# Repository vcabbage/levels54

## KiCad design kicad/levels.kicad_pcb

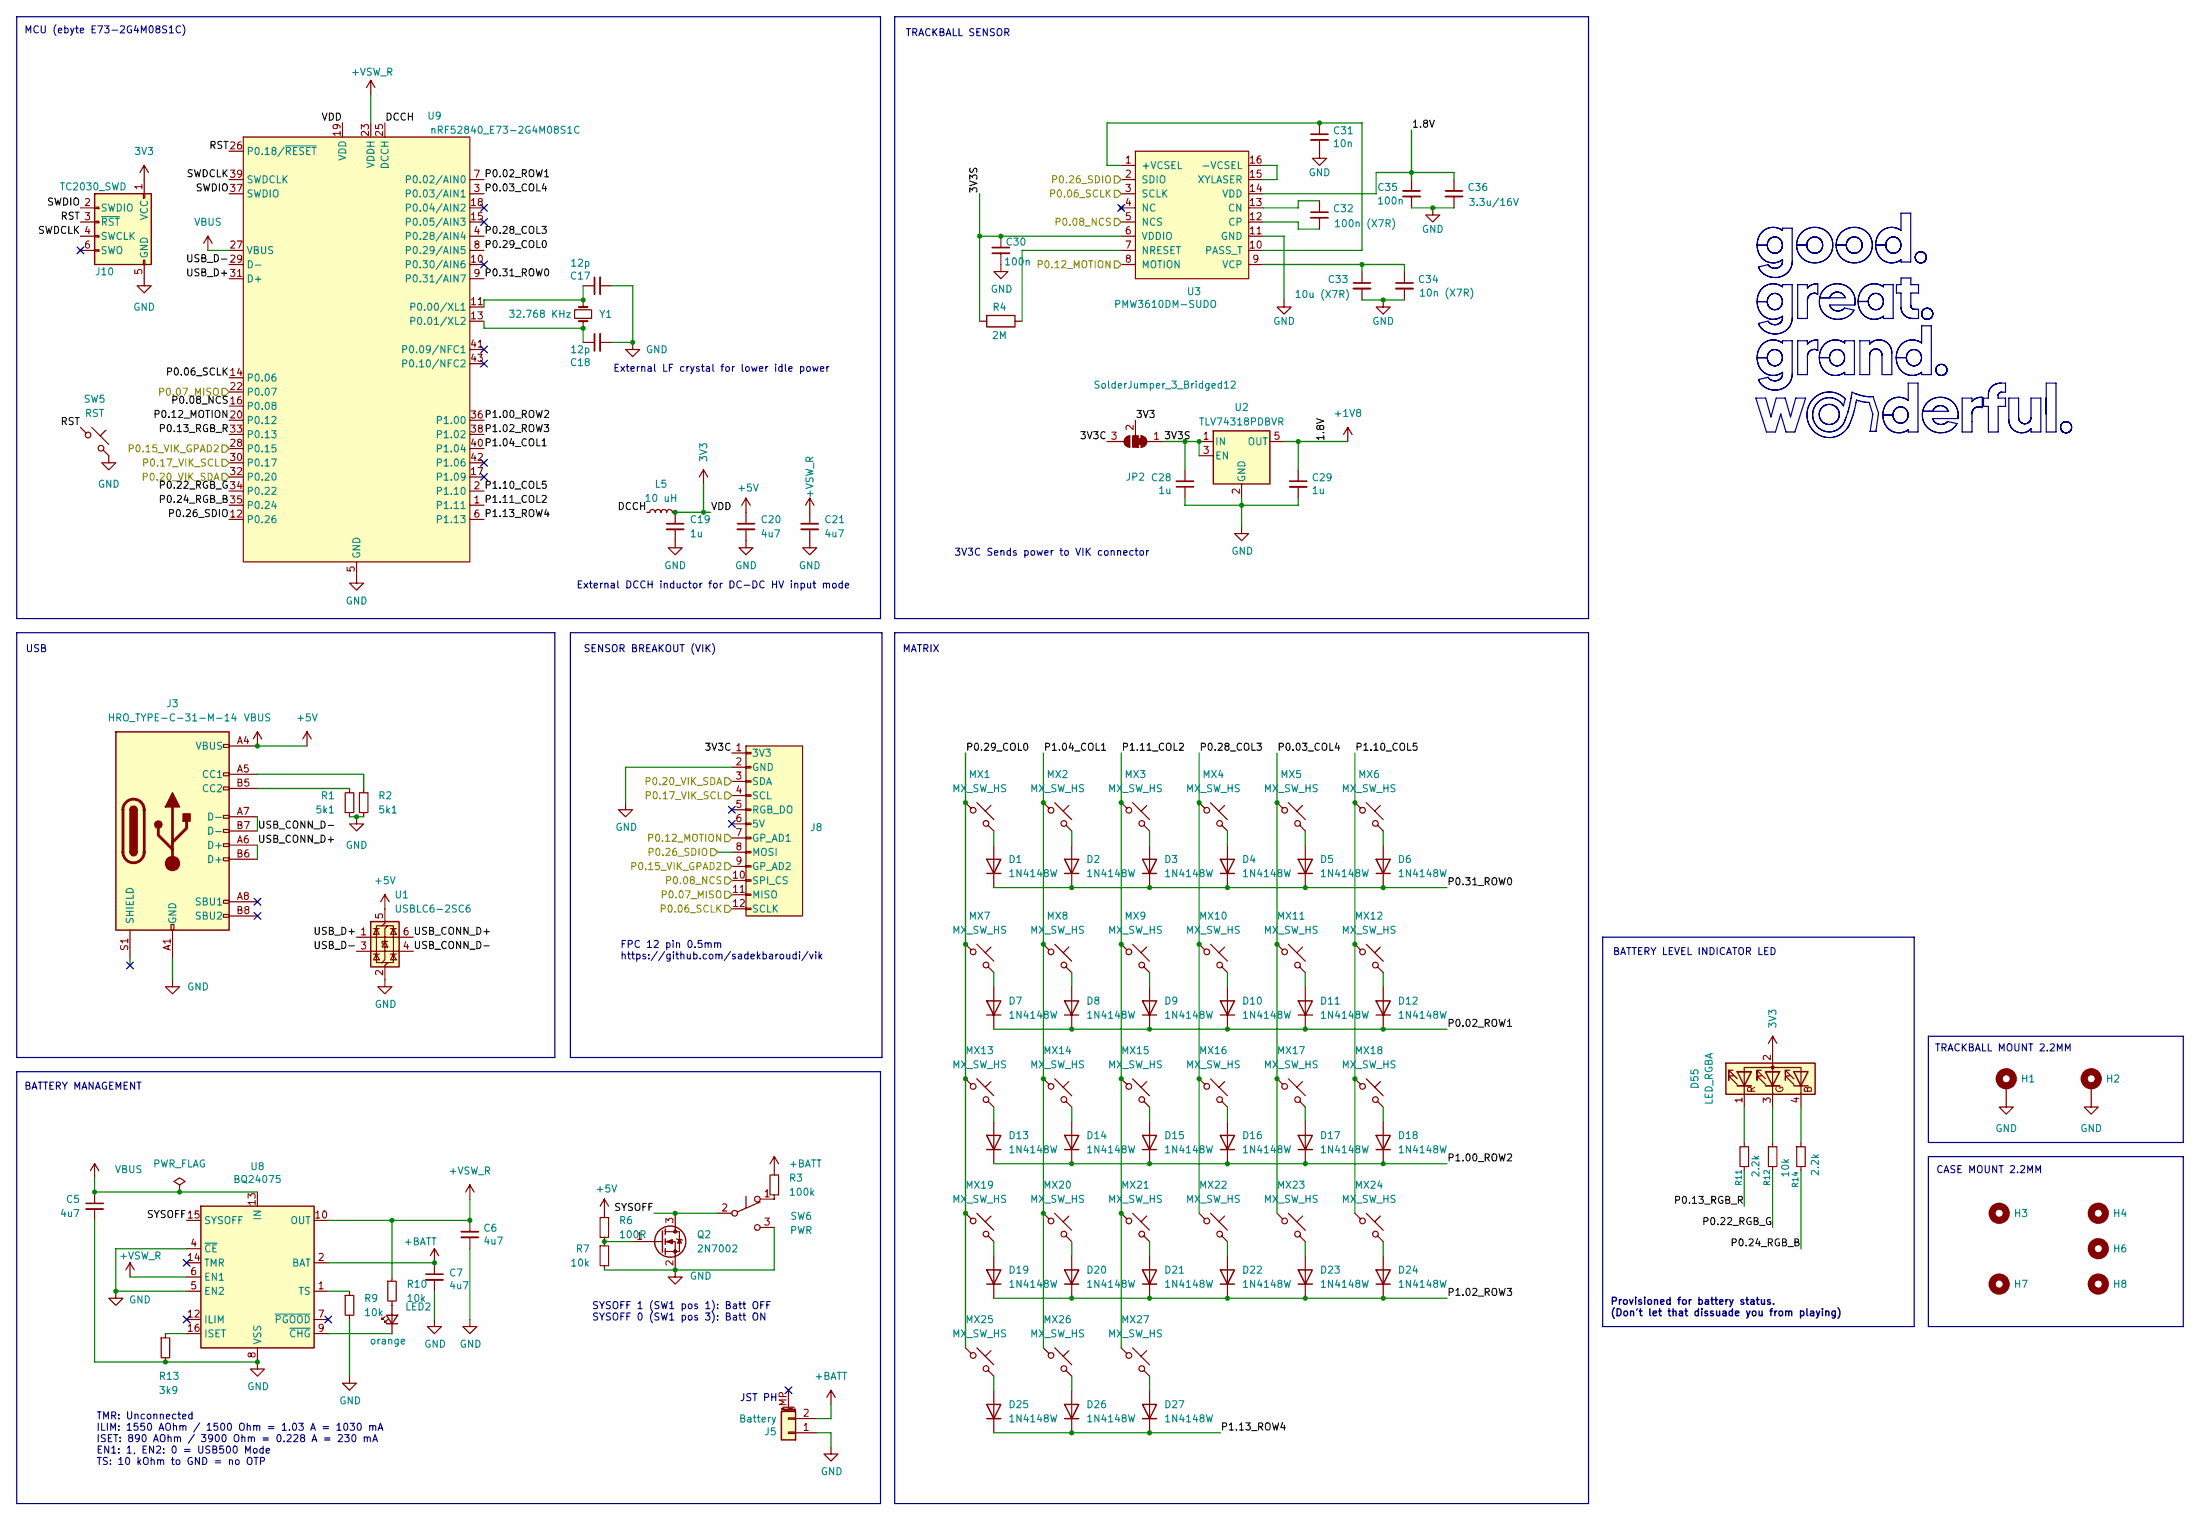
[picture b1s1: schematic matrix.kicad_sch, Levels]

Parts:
C5, C6, C7, C20, C21: 4u7; C_0402_1005Metric
C17, C18: 12p; C_0402_1005Metric
C19: 1u; C_0402_1005Metric
C28, C29: 1u; C_0603_1608Metric; LCSC C15849
C30, C35: 100n; C_0603_1608Metric; LCSC C14663
C31: 10n; C_0603_1608Metric; LCSC C57112
C32: 100n (X7R); C_0603_1608Metric; LCSC C14663
C33: 10u (X7R); C_0603_1608Metric; LCSC C237435
C34: 10n (X7R); C_0603_1608Metric; LCSC C57112
C36: 3.3u/16V; C_0603_1608Metric; LCSC C342962
D1, D2, D3, D4, D5, D6, D7, D8, D9, D10, D11, D12, D13, D14, D15, D16, D17, D18, D19, D20, D21, D22, D23, D24, D25, D26, D27: 1N4148W; D_SOD-123
D55: LED_RGBA; LED_NH-B1515RGBA-HF
H1, H2: MountingHole_Pad; MountingHole_2.2mm_M2_ISO7380_Pad
H3, H4, H6, H7: MountingHole; MountingHole_3.2mm_M3_DIN965
H8: MountingHole; MountingHole_2.2mm_M2_ISO7380
J3: HRO_TYPE-C-31-M-14; USB_C_Receptacle_HRO_TYPE-C-31-M-14
J5: Battery; JST_PH_S2B-PH-K_1x02_P2.00mm_Horizontal; LCSC C505023
J8: vik-keyboard-connector-horizontal
J10: TC2030_SWD; CON_TC2030_outlined
JP2: SolderJumper_3_Bridged12; SolderJumper-3_P1.3mm_Bridged12_RoundedPad1.0x1.5mm_NumberL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
L5: 10 uH; L_0603_1608Metric; LCSC C92982
LED2: orange; LED_0402_1005Metric
MX1, MX2, MX3, MX4, MX5, MX6, MX7, MX8, MX9, MX10, MX11, MX12, MX13, MX14, MX15, MX16, MX17, MX18, MX19, MX20, MX21, MX22, MX23, MX24, MX25, MX26, MX27: MX_SW_HS; SW_MX_HS_CPG151101S11_1u
Q2: 2N7002; SOT-23
R1, R2: 5k1; R_0402_1005Metric
R3: 100k; R_0402_1005Metric
R4: 2M; R_0603_1608Metric; LCSC C22976
R6: 100R; R_0402_1005Metric
R7, R9, R10, R12: 10k; R_0402_1005Metric
R11, R14: 2.2k; R_0402_1005Metric
R13: 3k9; R_0402_1005Metric
SW5: RST; SW_SPST_SKQG_WithStem
SW6: PWR; SW_MSK12C02-HB
U1: USBLC6-2SC6; SOT-23-6
U2: TLV74318PDBVR; SOT-23-5; LCSC C485152
U3: PMW3610DM-SUDO; PMW3610DM-SUDU 16Pin
U8: BQ24075; VQFN-16-1EP_3x3mm_P0.5mm_EP1.6x1.6mm
U9: nRF52840_E73-2G4M08S1C; LCSC C356849
Y1: 32.768 KHz; Crystal_SMD_2012-2Pin_2.0x1.2mm; LCSC C55208

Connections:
3V3: C19.1, D55.2 (A), J10.1 (VCC), JP2.2 (C), L5.2, U9.19 (VDD); also elsewhere on the board
+1V8: C29.1, C35.1, C36.1, U2.5 (OUT), U3.14 (VDD); also elsewhere on the board
+5V: C5.1, C20.1, J3.A4 (VBUS), J3.A9 (VBUS), J3.B4 (VBUS), J3.B9 (VBUS), R6.1, U1.5 (VBUS), U8.13 (IN), U9.27 (VBUS); also elsewhere on the board
+BATT: C7.1, J5.2, R3.2, U8.2 (BAT), U8.3 (BAT); also elsewhere on the board
+VSW_R: C6.1, C21.1, R10.1, U8.6 (EN1), U8.10 (OUT), U8.11 (OUT), U9.23 (VDDH)
/Right/3V3C: J8.1 (3V3), JP2.3 (B)
/Right/3V3S: C28.2, C30.1, JP2.1 (A), R4.2, U2.1 (IN), U2.3 (EN), U3.6 (VDDIO)
/Right/DCCH: L5.1, U9.25 (DCCH)
/Right/P0.02_ROW1: D7.1 (K), D8.1 (K), D9.1 (K), D10.1 (K), D11.1 (K), D12.1 (K), U9.7 (P0.02/AIN0)
/Right/P0.03_COL4: MX5.1, MX11.1, MX17.1, MX23.1, U9.3 (P0.03/AIN1)
/Right/P0.06_SCLK: J8.12 (SCLK), U3.3 (SCLK), U9.14 (P0.06)
/Right/P0.07_MISO: J8.11 (MISO), U9.22 (P0.07)
/Right/P0.08_NCS: J8.10 (SPI_CS), U3.5 (NCS), U9.16 (P0.08)
/Right/P0.12_MOTION: J8.7 (GP_AD1), U3.8 (MOTION), U9.20 (P0.12)
/Right/P0.13_RGB_R: R11.1, U9.33 (P0.13)
/Right/P0.15_VIK_GPAD2: J8.9 (GP_AD2), U9.28 (P0.15)
/Right/P0.17_VIK_SCL: J8.4 (SCL), U9.30 (P0.17)
/Right/P0.20_VIK_SDA: J8.3 (SDA), U9.32 (P0.20)
/Right/P0.22_RGB_G: R12.2, U9.34 (P0.22)
/Right/P0.24_RGB_B: R14.2, U9.35 (P0.24)
/Right/P0.26_SDIO: J8.8 (MOSI), U3.2 (SDIO), U9.12 (P0.26)
/Right/P0.28_COL3: MX4.1, MX10.1, MX16.1, MX22.1, U9.4 (P0.28/AIN4)
/Right/P0.29_COL0: MX1.1, MX7.1, MX13.1, MX19.1, MX25.1, U9.8 (P0.29/AIN5)
/Right/P0.31_ROW0: D1.1 (K), D2.1 (K), D3.1 (K), D4.1 (K), D5.1 (K), D6.1 (K), U9.9 (P0.31/AIN7)
/Right/P1.00_ROW2: D13.1 (K), D14.1 (K), D15.1 (K), D16.1 (K), D17.1 (K), D18.1 (K), U9.36 (P1.00)
/Right/P1.02_ROW3: D19.1 (K), D20.1 (K), D21.1 (K), D22.1 (K), D23.1 (K), D24.1 (K), U9.38 (P1.02)
/Right/P1.04_COL1: MX2.1, MX8.1, MX14.1, MX20.1, MX26.1, U9.40 (P1.04)
/Right/P1.10_COL5: MX6.1, MX12.1, MX18.1, MX24.1, U9.2 (P1.10)
/Right/P1.11_COL2: MX3.1, MX9.1, MX15.1, MX21.1, MX27.1, U9.1 (P1.11)
/Right/P1.13_ROW4: D25.1 (K), D26.1 (K), D27.1 (K), U9.6 (P1.13)
/Right/RST: J10.3 (~RST), SW5.1, U9.26 (P0.18/~RESET)
/Right/SWDCLK: J10.4 (SWCLK), U9.39 (SWDCLK)
/Right/SWDIO: J10.2 (SWDIO), U9.37 (SWDIO)
/Right/SYSOFF: Q2.3 (D), SW6.2 (B), U8.15 (SYSOFF)
/Right/USB_CONN_D+: J3.A6 (D+), J3.B6 (D+), U1.6 (I/O1)
/Right/USB_CONN_D-: J3.A7 (D-), J3.B7 (D-), U1.4 (I/O2)
/Right/USB_D+: U1.1 (I/O1), U9.31 (D+)
/Right/USB_D-: U1.3 (I/O2), U9.29 (D-)
GND: C5.2, C6.2, C7.2, C17.2, C18.2, C19.2, C20.2, C21.2, C28.1, C29.2, C30.2, C31.2, C33.2, C34.2, C35.2, C36.2, H1.1, H2.1, J3.A1 (GND), J3.A12 (GND), J3.B1 (GND), J3.B12 (GND), J5.1, J8.2 (GND), J10.5 (GND), Q2.2 (S), R1.1, R2.1, R7.2, R9.2, R13.2, SW5.2, SW6.3 (C), U1.2 (GND), U2.2 (GND), U3.11 (GND), U8.4 (~CE), U8.5 (EN2), U8.8 (VSS), U8.17 (VSS), U9.5 (GND), U9.21 (GND), U9.24 (GND); also elsewhere on the board
unnamed: D1.2 (A), MX1.2
unnamed: D2.2 (A), MX2.2
unnamed: D3.2 (A), MX3.2
unnamed: D4.2 (A), MX4.2
unnamed: D5.2 (A), MX5.2
unnamed: D6.2 (A), MX6.2
unnamed: D7.2 (A), MX7.2
unnamed: D8.2 (A), MX8.2
unnamed: D9.2 (A), MX9.2
unnamed: D10.2 (A), MX10.2
unnamed: D11.2 (A), MX11.2
unnamed: D12.2 (A), MX12.2
unnamed: D13.2 (A), MX13.2
unnamed: D14.2 (A), MX14.2
unnamed: D15.2 (A), MX15.2
unnamed: D16.2 (A), MX16.2
unnamed: D17.2 (A), MX17.2
unnamed: D18.2 (A), MX18.2
unnamed: D19.2 (A), MX19.2
unnamed: D20.2 (A), MX20.2
unnamed: D21.2 (A), MX21.2
unnamed: D22.2 (A), MX22.2
unnamed: D23.2 (A), MX23.2
unnamed: D24.2 (A), MX24.2
unnamed: D25.2 (A), MX25.2
unnamed: D26.2 (A), MX26.2
unnamed: D27.2 (A), MX27.2
unnamed: D55.4 (BK), R14.1
unnamed: D55.3 (GK), R12.1
unnamed: D55.1 (RK), R11.2
unnamed: J3.A5 (CC1), R2.2
unnamed: J3.B5 (CC2), R1.2
unnamed: LED2.2 (A), R10.2
unnamed: LED2.1 (K), U8.9 (~CHG)
unnamed: Q2.1 (G), R6.2, R7.1
unnamed: R3.1, SW6.1 (A)
unnamed: C31.1, U3.1 (+VCSEL), U3.10 (PASS_T)
unnamed: U3.15 (XYLASER), U3.16 (-VCSEL)
unnamed: C32.1, U3.13 (CN)
unnamed: C32.2, U3.12 (CP)
unnamed: R4.1, U3.7 (NRESET)
unnamed: C33.1, C34.1, U3.9 (VCP)
unnamed: R13.1, U8.16 (ISET)
unnamed: R9.1, U8.1 (TS)
unnamed: C17.1, U9.11 (P0.00/XL1), Y1.2
unnamed: C18.1, U9.13 (P0.01/XL2), Y1.1

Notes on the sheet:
BATTERY LEVEL INDICATOR LED
JST PH
Provisioned for battery status. (Don't let that dissuade you from playing)
MCU (ebyte E73-2G4M08S1C)
TRACKBALL SENSOR
SENSOR BREAKOUT (VIK)
TMR: Unconnected ILIM: 1550 AOhm / 1500 Ohm = 1.03 A = 1030 mA ISET: 890 AOhm / 3900 Ohm = 0.228 A = 230 mA EN1: 1, EN2: 0 = USB500 Mode TS: 10 kOhm to GND = no OTP
FPC 12 pin 0.5mm https://github.com/sadekbaroudi/vik
BATTERY MANAGEMENT
USB
CASE MOUNT 2.2MM
3V3C Sends power to VIK connector
External LF crystal for lower idle power
MATRIX
SYSOFF 1 (SW1 pos 1): Batt OFF SYSOFF 0 (SW1 pos 3): Batt ON
External DCCH inductor for DC-DC HV input mode
TRACKBALL MOUNT 2.2MM

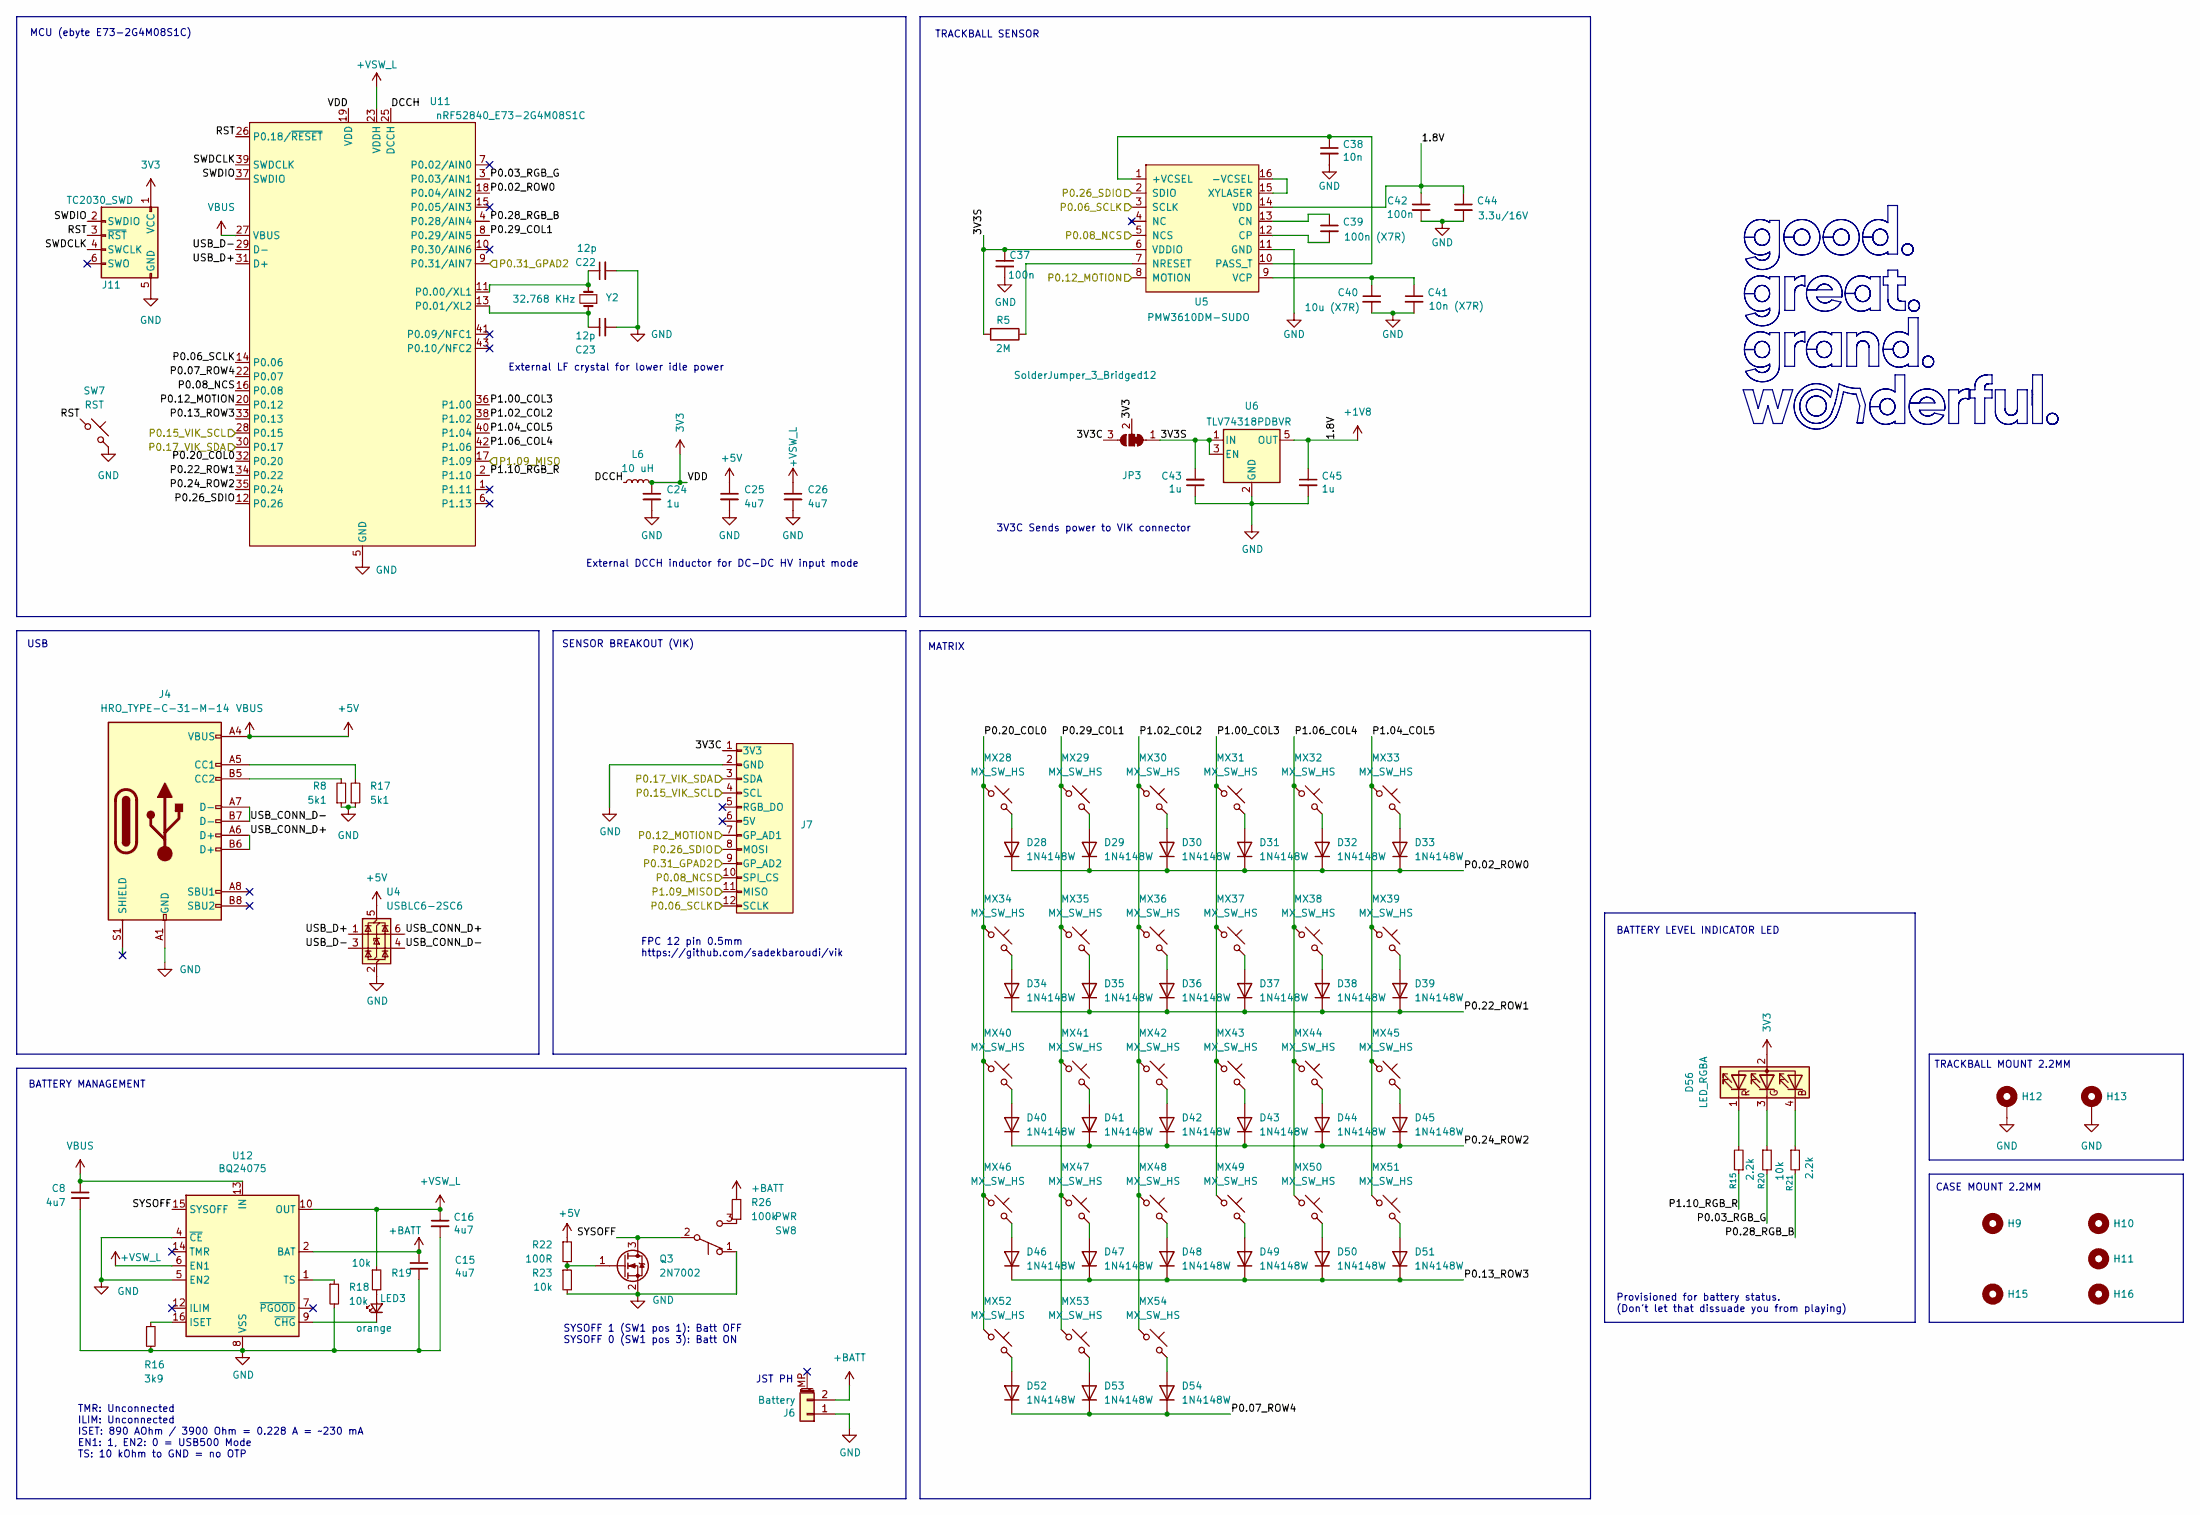
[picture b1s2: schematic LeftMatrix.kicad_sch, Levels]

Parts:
C8, C15, C16, C25, C26: 4u7; C_0402_1005Metric
C22, C23: 12p; C_0402_1005Metric
C24: 1u; C_0402_1005Metric
C37, C42: 100n; C_0603_1608Metric; LCSC C14663
C38: 10n; C_0603_1608Metric; LCSC C57112
C39: 100n (X7R); C_0603_1608Metric; LCSC C14663
C40: 10u (X7R); C_0603_1608Metric; LCSC C237435
C41: 10n (X7R); C_0603_1608Metric; LCSC C57112
C43, C45: 1u; C_0603_1608Metric; LCSC C15849
C44: 3.3u/16V; C_0603_1608Metric; LCSC C342962
D28, D29, D30, D31, D32, D33, D34, D35, D36, D37, D38, D39, D40, D41, D42, D43, D44, D45, D46, D47, D48, D49, D50, D51, D52, D53, D54: 1N4148W; D_SOD-123
D56: LED_RGBA; LED_NH-B1515RGBA-HF
H9, H10, H11, H15: MountingHole; MountingHole_2.2mm_M2_ISO7380
H12, H13: MountingHole_Pad; MountingHole_2.2mm_M2_ISO7380_Pad
H16: MountingHole; MountingHole_3.2mm_M3_DIN965
J4: HRO_TYPE-C-31-M-14; USB_C_Receptacle_HRO_TYPE-C-31-M-14
J6: Battery; JST_PH_S2B-PH-K_1x02_P2.00mm_Horizontal; LCSC C505023
J7: vik-keyboard-connector-horizontal
J11: TC2030_SWD; CON_TC2030_outlined
JP3: SolderJumper_3_Bridged12; SolderJumper-3_P1.3mm_Bridged12_RoundedPad1.0x1.5mm_NumberL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
L6: 10 uH; L_0603_1608Metric; LCSC C92982
LED3: orange; LED_0402_1005Metric
MX28, MX29, MX30, MX31, MX32, MX33, MX34, MX35, MX36, MX37, MX38, MX39, MX40, MX41, MX42, MX43, MX44, MX45, MX46, MX47, MX48, MX49, MX50, MX51, MX52, MX53, MX54: MX_SW_HS; SW_MX_HS_CPG151101S11_1u
Q3: 2N7002; SOT-23
R5: 2M; R_0603_1608Metric; LCSC C22976
R8, R17: 5k1; R_0402_1005Metric
R15, R21: 2.2k; R_0402_1005Metric
R16: 3k9; R_0402_1005Metric
R18, R19, R20, R23: 10k; R_0402_1005Metric
R22: 100R; R_0402_1005Metric
R26: 100k; R_0402_1005Metric
SW7: RST; SW_SPST_SKQG_WithStem
SW8: PWR; SW_MSK12C02-HB
U4: USBLC6-2SC6; SOT-23-6
U5: PMW3610DM-SUDO; PMW3610DM-SUDU 16Pin
U6: TLV74318PDBVR; SOT-23-5; LCSC C485152
U11: nRF52840_E73-2G4M08S1C; LCSC C356849
U12: BQ24075; VQFN-16-1EP_3x3mm_P0.5mm_EP1.6x1.6mm
Y2: 32.768 KHz; Crystal_SMD_2012-2Pin_2.0x1.2mm; LCSC C55208

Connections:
3V3: C24.1, D56.2 (A), J11.1 (VCC), JP3.2 (C), L6.2, U11.19 (VDD); also elsewhere on the board
+1V8: C42.1, C44.1, C45.1, U5.14 (VDD), U6.5 (OUT); also elsewhere on the board
+5V: C8.1, C25.1, J4.A4 (VBUS), J4.A9 (VBUS), J4.B4 (VBUS), J4.B9 (VBUS), R22.1, U4.5 (VBUS), U11.27 (VBUS), U12.13 (IN); also elsewhere on the board
+BATT: C15.1, J6.2, R26.2, U12.2 (BAT), U12.3 (BAT); also elsewhere on the board
+VSW_L: C16.1, C26.1, R19.1, U11.23 (VDDH), U12.6 (EN1), U12.10 (OUT), U12.11 (OUT)
/Left/3V3C: J7.1 (3V3), JP3.3 (B)
/Left/3V3S: C37.1, C43.2, JP3.1 (A), R5.2, U5.6 (VDDIO), U6.1 (IN), U6.3 (EN)
/Left/DCCH: L6.1, U11.25 (DCCH)
/Left/P0.02_ROW0: D28.1 (K), D29.1 (K), D30.1 (K), D31.1 (K), D32.1 (K), D33.1 (K), U11.18 (P0.04/AIN2)
/Left/P0.03_RGB_G: R20.2, U11.3 (P0.03/AIN1)
/Left/P0.06_SCLK: J7.12 (SCLK), U5.3 (SCLK), U11.14 (P0.06)
/Left/P0.07_ROW4: D52.1 (K), D53.1 (K), D54.1 (K), U11.22 (P0.07)
/Left/P0.08_NCS: J7.10 (SPI_CS), U5.5 (NCS), U11.16 (P0.08)
/Left/P0.12_MOTION: J7.7 (GP_AD1), U5.8 (MOTION), U11.20 (P0.12)
/Left/P0.13_ROW3: D46.1 (K), D47.1 (K), D48.1 (K), D49.1 (K), D50.1 (K), D51.1 (K), U11.33 (P0.13)
/Left/P0.15_VIK_SCL: J7.4 (SCL), U11.28 (P0.15)
/Left/P0.17_VIK_SDA: J7.3 (SDA), U11.30 (P0.17)
/Left/P0.20_COL0: MX28.1, MX34.1, MX40.1, MX46.1, MX52.1, U11.32 (P0.20)
/Left/P0.22_ROW1: D34.1 (K), D35.1 (K), D36.1 (K), D37.1 (K), D38.1 (K), D39.1 (K), U11.34 (P0.22)
/Left/P0.24_ROW2: D40.1 (K), D41.1 (K), D42.1 (K), D43.1 (K), D44.1 (K), D45.1 (K), U11.35 (P0.24)
/Left/P0.26_SDIO: J7.8 (MOSI), U5.2 (SDIO), U11.12 (P0.26)
/Left/P0.28_RGB_B: R21.2, U11.4 (P0.28/AIN4)
/Left/P0.29_COL1: MX29.1, MX35.1, MX41.1, MX47.1, MX53.1, U11.8 (P0.29/AIN5)
/Left/P0.31_GPAD2: J7.9 (GP_AD2), U11.9 (P0.31/AIN7)
/Left/P1.00_COL3: MX31.1, MX37.1, MX43.1, MX49.1, U11.36 (P1.00)
/Left/P1.02_COL2: MX30.1, MX36.1, MX42.1, MX48.1, MX54.1, U11.38 (P1.02)
/Left/P1.04_COL5: MX33.1, MX39.1, MX45.1, MX51.1, U11.40 (P1.04)
/Left/P1.06_COL4: MX32.1, MX38.1, MX44.1, MX50.1, U11.42 (P1.06)
/Left/P1.09_MISO: J7.11 (MISO), U11.17 (P1.09)
/Left/P1.10_RGB_R: R15.1, U11.2 (P1.10)
/Left/RST: J11.3 (~RST), SW7.1, U11.26 (P0.18/~RESET)
/Left/SWDCLK: J11.4 (SWCLK), U11.39 (SWDCLK)
/Left/SWDIO: J11.2 (SWDIO), U11.37 (SWDIO)
/Left/SYSOFF: Q3.3 (D), SW8.2 (B), U12.15 (SYSOFF)
/Left/USB_CONN_D+: J4.A6 (D+), J4.B6 (D+), U4.6 (I/O1)
/Left/USB_CONN_D-: J4.A7 (D-), J4.B7 (D-), U4.4 (I/O2)
/Left/USB_D+: U4.1 (I/O1), U11.31 (D+)
/Left/USB_D-: U4.3 (I/O2), U11.29 (D-)
GND: C8.2, C15.2, C16.2, C22.2, C23.2, C24.2, C25.2, C26.2, C37.2, C38.2, C40.2, C41.2, C42.2, C43.1, C44.2, C45.2, H12.1, H13.1, J4.A1 (GND), J4.A12 (GND), J4.B1 (GND), J4.B12 (GND), J6.1, J7.2 (GND), J11.5 (GND), Q3.2 (S), R8.1, R16.2, R17.1, R18.2, R23.2, SW7.2, SW8.1 (A), U4.2 (GND), U5.11 (GND), U6.2 (GND), U11.5 (GND), U11.21 (GND), U11.24 (GND), U12.4 (~CE), U12.5 (EN2), U12.8 (VSS), U12.17 (VSS); also elsewhere on the board
unnamed: D28.2 (A), MX28.2
unnamed: D29.2 (A), MX29.2
unnamed: D30.2 (A), MX30.2
unnamed: D31.2 (A), MX31.2
unnamed: D32.2 (A), MX32.2
unnamed: D33.2 (A), MX33.2
unnamed: D34.2 (A), MX34.2
unnamed: D35.2 (A), MX35.2
unnamed: D36.2 (A), MX36.2
unnamed: D37.2 (A), MX37.2
unnamed: D38.2 (A), MX38.2
unnamed: D39.2 (A), MX39.2
unnamed: D40.2 (A), MX40.2
unnamed: D41.2 (A), MX41.2
unnamed: D42.2 (A), MX42.2
unnamed: D43.2 (A), MX43.2
unnamed: D44.2 (A), MX44.2
unnamed: D45.2 (A), MX45.2
unnamed: D46.2 (A), MX46.2
unnamed: D47.2 (A), MX47.2
unnamed: D48.2 (A), MX48.2
unnamed: D49.2 (A), MX49.2
unnamed: D50.2 (A), MX50.2
unnamed: D51.2 (A), MX51.2
unnamed: D52.2 (A), MX52.2
unnamed: D53.2 (A), MX53.2
unnamed: D54.2 (A), MX54.2
unnamed: D56.4 (BK), R21.1
unnamed: D56.3 (GK), R20.1
unnamed: D56.1 (RK), R15.2
unnamed: J4.A5 (CC1), R17.2
unnamed: J4.B5 (CC2), R8.2
unnamed: LED3.2 (A), R19.2
unnamed: LED3.1 (K), U12.9 (~CHG)
unnamed: Q3.1 (G), R22.2, R23.1
unnamed: R26.1, SW8.3 (C)
unnamed: C38.1, U5.1 (+VCSEL), U5.10 (PASS_T)
unnamed: U5.15 (XYLASER), U5.16 (-VCSEL)
unnamed: C39.1, U5.13 (CN)
unnamed: C39.2, U5.12 (CP)
unnamed: R5.1, U5.7 (NRESET)
unnamed: C40.1, C41.1, U5.9 (VCP)
unnamed: C22.1, U11.11 (P0.00/XL1), Y2.2
unnamed: C23.1, U11.13 (P0.01/XL2), Y2.1
unnamed: R16.1, U12.16 (ISET)
unnamed: R18.1, U12.1 (TS)

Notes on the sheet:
External LF crystal for lower idle power
JST PH
BATTERY MANAGEMENT
Provisioned for battery status. (Don't let that dissuade you from playing)
BATTERY LEVEL INDICATOR LED
TRACKBALL MOUNT 2.2MM
CASE MOUNT 2.2MM
USB
External DCCH inductor for DC-DC HV input mode
MATRIX
TRACKBALL SENSOR
3V3C Sends power to VIK connector
FPC 12 pin 0.5mm https://github.com/sadekbaroudi/vik
TMR: Unconnected ILIM: Unconnected ISET: 890 AOhm / 3900 Ohm = 0.228 A = ~230 mA EN1: 1, EN2: 0 = USB500 Mode TS: 10 kOhm to GND = no OTP
SENSOR BREAKOUT (VIK)
MCU (ebyte E73-2G4M08S1C)
SYSOFF 1 (SW1 pos 1): Batt OFF SYSOFF 0 (SW1 pos 3): Batt ON

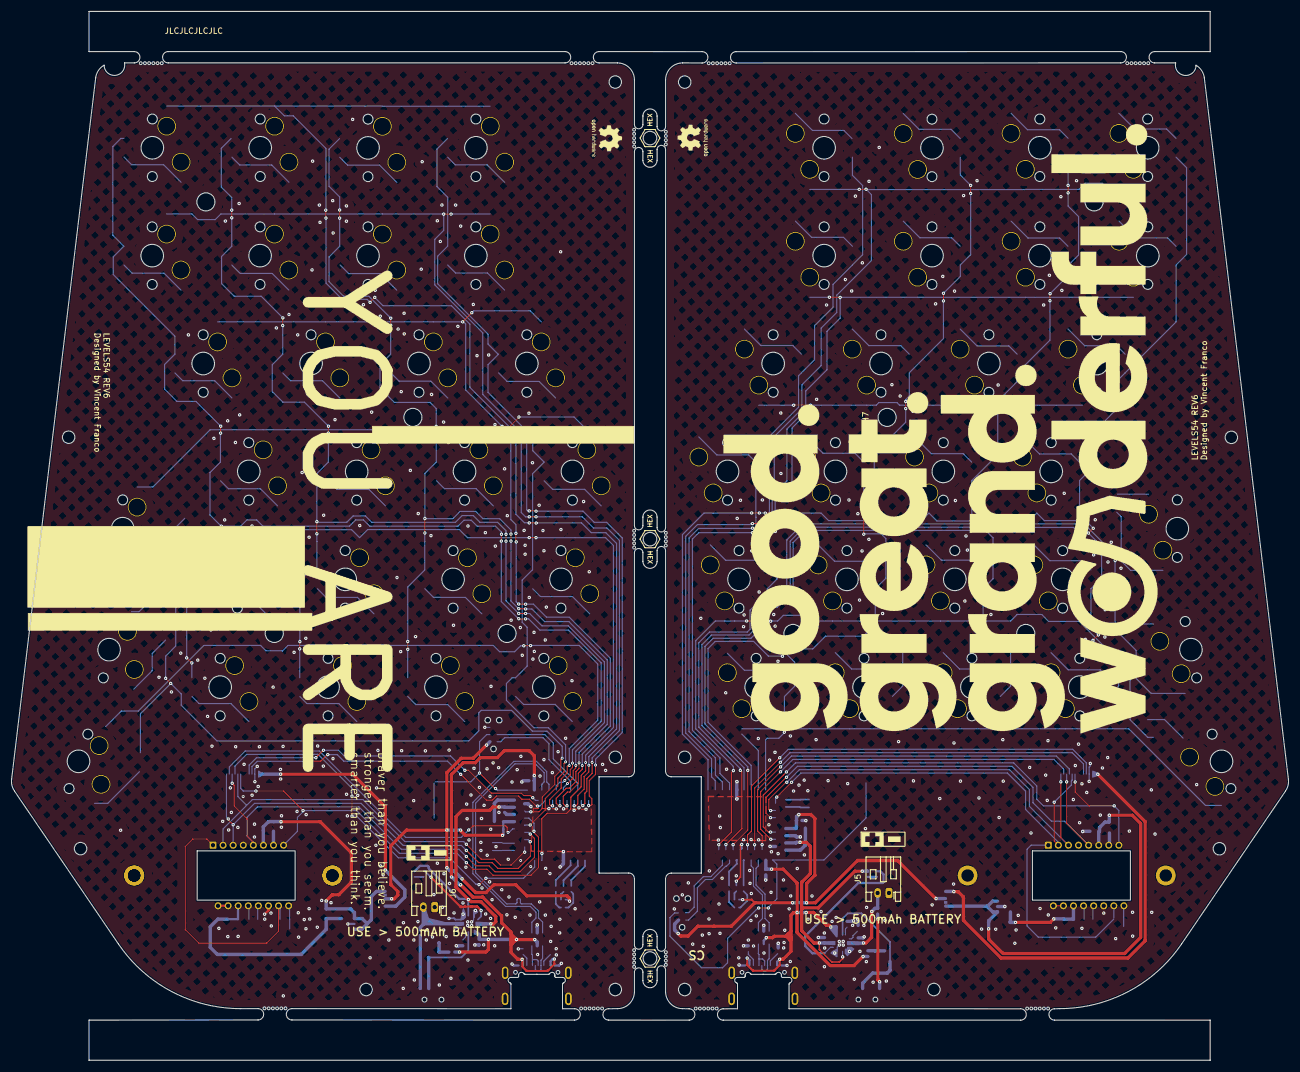
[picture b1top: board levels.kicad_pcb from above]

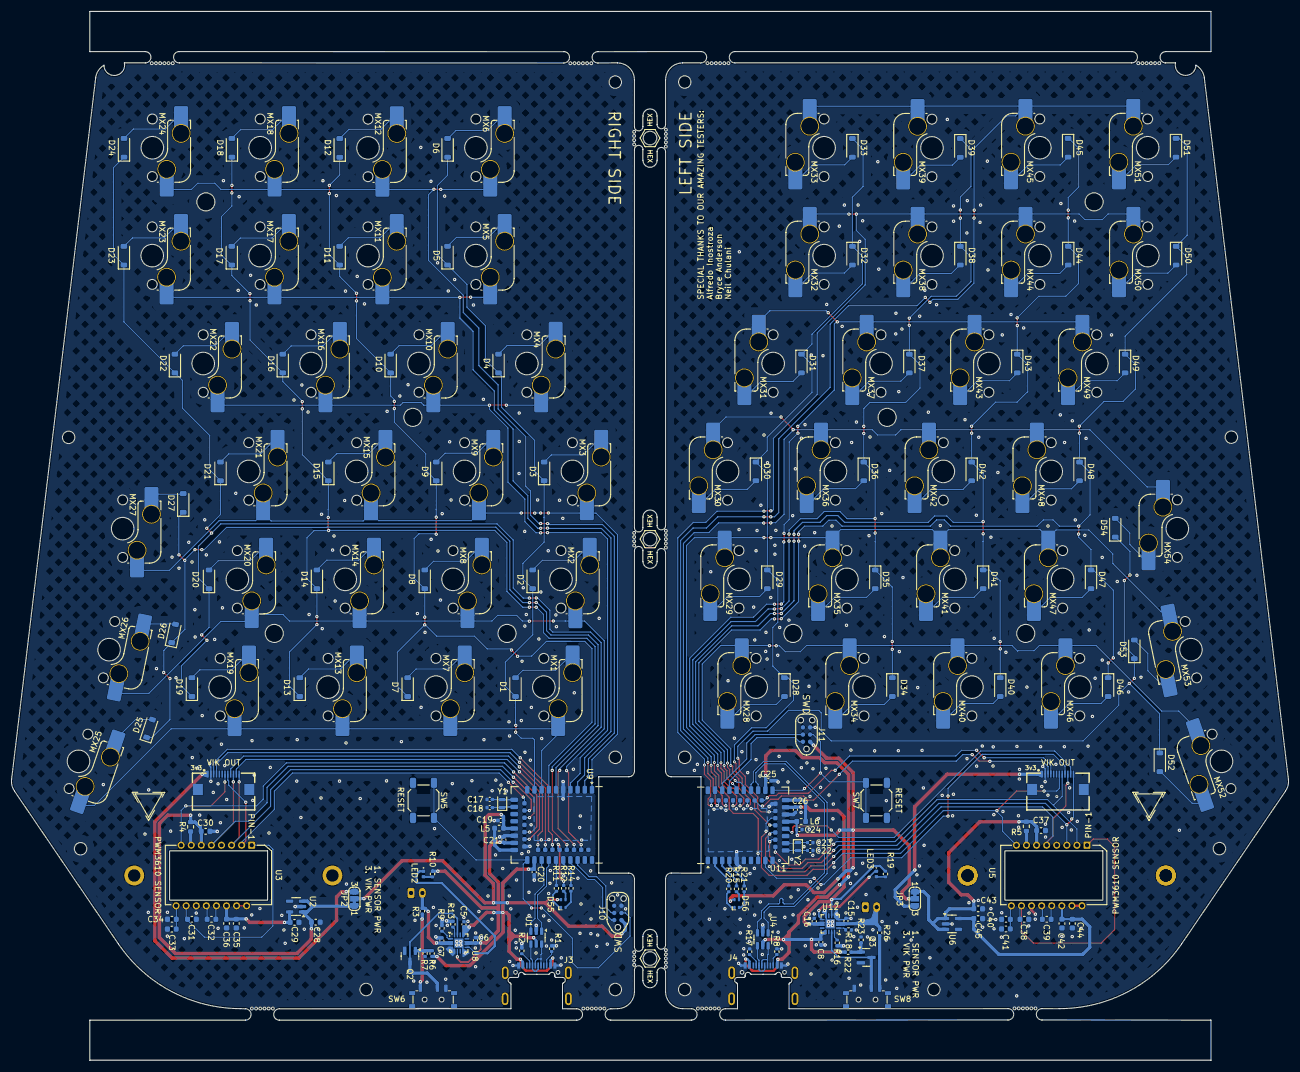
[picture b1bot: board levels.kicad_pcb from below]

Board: 2 copper layers, 225.5 x 185.2 mm, 229 parts (201 on the bottom side), 165 nets.

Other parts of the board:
H1#2, H2#2: MountingHole_Pad; MountingHole_2.2mm_M2_ISO7380_Pad
H3#2, H4#2, H7#2: MountingHole; MountingHole_3.2mm_M3_DIN965
H8#2, H8#3, H8#4, H8#5, H8#6, H8#7, H8#8: MountingHole; MountingHole_2.2mm_M2_ISO7380
MB5, MB5#2, MB5#3: 5.5mm; mousebites_5p5mm_easysnap

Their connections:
GND: H1#2.1, H2#2.1; also elsewhere on the board

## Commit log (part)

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2026-05-02 Gitignore
2026-05-02 Open sourcing Levels PCBs
2026-05-03 Adding docs
2026-05-24 License
